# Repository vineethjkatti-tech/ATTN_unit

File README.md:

# ATTN_unit
A smart desk companion that tracks your focus using sound, motion, and time. It gives real-time feedback, builds study streaks, and adapts to your habits to help you stay locked in. Stay focused. It’s watching.
It is a device that helps you focus while studying, working etc. The main purpose of this device is to gameify maintaining focus and helps us achieve concentration.

# Overview
Fitted with the **Esp32 Dev Board**, **ATTN_unit** uses **I2S MEMS Breakout Board** and **HLK-LD2410** sensors to read the noise levels and movment of the user and gives out the **Focus Score** of the user and also displays corresponding emotions the **2.13 Inch E-Ink Display**. It includes a **2 pin tactile switch** to start or stop a study session.

## Zine Page

_Check out my zine_page [here!!](https://github.com/vineethjkatti-tech/ATTN_unit/blob/main/ATTN_unit-zine.pdf)

# How it works
This project has four key elements:

**1. Memory**
>It uses an ESP32 so basically in - built memory that stays even after restart. It uses memory data for long term analysis.

**2. Personality:**
>Yes! it has a personality you can influence its personality. For example, if you are distracted a lot of the times it is more stricter on you and if your more focused on the other hand, it is more kind..

**3. Sensor Reading:**
>It reads data from various sensors on the esp namely - microphone(noise level), motion sensor(for your movment sensation) and also a push button(to start or end session).

**4. Reward Logic**
>This the highlight of my project. There is one core factor - **consistency score** which is affected by many factors such as your **focus**, the **noise level** in your environment, your **movment** - how much you fidget around and its **state **_(which is affected by noise level, focus and motion)._

## Firmware Logic
The code contains a lot of **variables** and custom **functions**. It has a **Scoring System** and also contains **Memory**. The UI is good and it contains a character called **EYES** who always keeps watch on you and craves for your **attention**.

### Structure
When we come to the hardware side, ATTN_unit contains two parts:
1. **Part A:** The Front Panel with the screen bezel and the screen itself.
2. **Part B:** The main container that holds the PCB and to which the Part A is snapped onto

**Connection Methods:**
There are two types of connection methods used in this project
1. **Snap-in Locks-**
  - It is used to fit Part A and B together.
  - It is used to fit the display onto its bezel.

2. **M3 Heat Inserts-**
  - They are used to connect the PCB with Part B.

**Display:**
As the **2.13 Inch 2 color E-Ink display** is native to one of the raspberry pi, I have to keep in mind some things while connecting it to ESP32.
The JST on the display accomodates **8-sockets** as you may know. I have provided an **8-pin header** on my PCB which has the same pin designations as the JST on the the display. The JST can be connected to the header using jumper wires. 

# Steps to Build ATTN_unit
**All the required materials to make the project can be found in the BOM file!!**

1. Start by printing all the requires plastic material. (All CAD files can be found [here](https://github.com/vineethjkatti-tech/ATTN_unit/tree/main/CAD))

2. Next, mount the PCB (it doesnt matter if you solder one, you can find all the schematics [here](https://github.com/vineethjkatti-tech/ATTN_unit/tree/main/KICAD)) to the standoffs in **Part B** using **M3 Inserts and Screws**.

3. After that put the display into Part A by just pressing it in ( the Part has snap-in locks in the bezel space ).

4. Then screw an **8mm momentary switch** through the hole in the **right side** of **Part B**. Solder the two pins to their resepctive pins on ESP32 (One to **GND** and another one to any **GPIO pin**)

5. After this connect the **Front Panel** and **Part B** by pressing them into each other cause they have **snap-in locks**.

6. Last step is to connect the ESP32 to a USB Port for Power Supply and your done!!

**_If you followed all the steps, then congrats!! Your ATTN_unit is ready. Enjoy your fulfilling and focus-filled study sessions!!_**

# Why this Project?
In a world with thousands of distractions around us, it is hard for students to focus and concentrate on studying. These study sessions are often plain and lack something **fun**. This lack of _fun_ is satisfied by our **ATTN_unit**. It makes studying feel like a game by introducing **Focus Score** and others such elements that **encourage** students to study.

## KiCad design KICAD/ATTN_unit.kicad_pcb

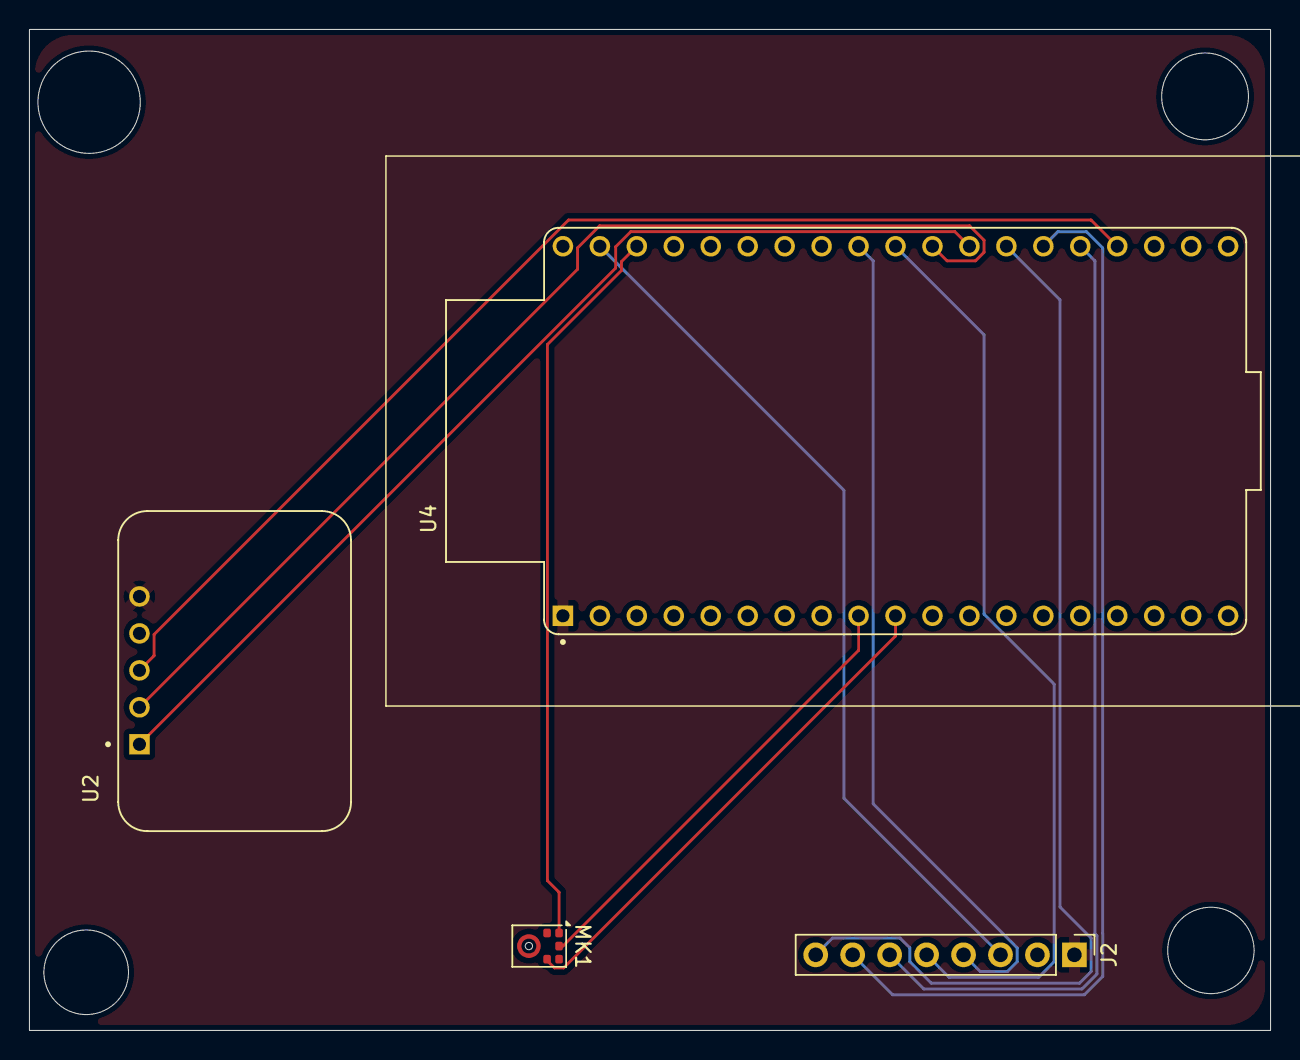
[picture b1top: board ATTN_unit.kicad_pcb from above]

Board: 2 copper layers, 85.3 x 68.8 mm, 4 parts (0 on the bottom side), 14 nets.

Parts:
J2: Screen Connector; PinHeader_1x08_P2.54mm_Vertical
MK1: SPH0645LM4H; Knowles_SPH0645LM4H-6_3.5x2.65mm
U2: HLK-LD2410C; MODULE_HLK-LD2410C
U4: ESP32-DEVKITC-32E; ESP32

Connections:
unnamed: J2.8 (BUSY), U4.J3_13 (IO4)
unnamed: J2.4 (CLK), U4.J3_9 (IO18)
unnamed: J2.5 (CS), U4.J3_10 (IO5)
unnamed: J2.6 (DC), U4.J3_15 (IO2)
unnamed: J2.3 (DIN), U4.J3_2 (IO23)
unnamed: J2.2 (GND), MK1.2 (SEL), MK1.3 (GND), U2.4 (GND), U4.J3_1 (GND_J3_1)
unnamed: J2.7 (RST), U4.J3_14 (IO0)
unnamed: J2.1 (VCC), MK1.5 (VDD), U2.5 (VCC), U4.J2_1 (3V3)
unnamed: MK1.4 (BCLK), U4.J2_10 (IO26)
unnamed: MK1.6 (DATA), U4.J2_9 (IO25)
unnamed: MK1.1 (WS), U4.J3_3 (IO22)
unnamed: U2.3 (OUT), U4.J3_16 (IO15)
unnamed: U2.2 (UART_RX), U4.J3_11 (IO17)
unnamed: U2.1 (UART_TX), U4.J3_12 (IO16)

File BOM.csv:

Name ,Qty,Price ($),Link
KY038 Sensor,1,1.88,https://www.amazon.in/roboCraze-Robocraze-Sound-Sensor-Modul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
Tactile Switch (2 pin),1,0.1,https://www.amazon.in/Push-Button-Tactile-Micro-Switch/dp/B0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
0.96 inch OLED display,1,2.18,https://robu.in/product/0-96-inch-ssd1306-white-oled-display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
HLK-LD2410C Sensor,1,5.26,https://robu.in/product/hi-link-hlk-ld2410c-p-24ghz-human-pr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
ESP32-DEVKITC-32E,1,3.54,https://robu.in/product/esp-wroom-32-esp32-wifi-bt-ble-mcu-module/
M2 Inserts,8,0.4,https://robu.in/product/m2-x-4-mm-brass-insert/
M2 Screws,8,0.7,https://robu.in/product/m2-x-8mm-socket-button-head-cap-alle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
M3 Inserts,4,0.24,https://www.amazon.in/Insert-Threaded-Printing-Woodworking-P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
M3 Screws,4,0.212,https://www.amazon.in/Rpi-shop-tensile-Machine-Quantity/dp/B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
Shipping Costs,-,~10,-
Grand Total ,,24.512,-

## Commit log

2026-05-01 Create hi
2026-05-01 Fix grammar and clarity in README personality section
    Corrected grammatical errors and improved clarity in the personality section.
2026-05-01 Fix typos and enhance formatting in README
    Corrected typos and improved formatting in the README.
2026-05-11 Added Large Files
2026-05-11 Add 'Why this Project?' section to README
    Added a section explaining the purpose of the project.
2026-05-12 Add image to README for device illustration
    Added an image to illustrate the device's features.
2026-05-12 Fix typo in README.md
2026-05-12 Update README with build steps and resources
    Added instructions for building the ATTN_unit and included links to design and CAD files.
2026-05-13 Fix typo in README about character 'EYES'
    Corrected a typo in the README regarding the character 'EYES'.
2026-05-13 Deleted Duplicates and Organized Repository.
2026-05-13 Rename ATTN_unit.csv to BOM.csv
2026-05-17 Add pixel art light bulb simulator
    - Created a new `simulator/` directory.
    - Implemented `index.html`, `style.css`, and `script.js`.
    - Used CSS box-shadow technique for pixel art representation of Standard, Edison, and Globe bulbs.
    - Added power toggle and bulb type selection functionality.
    - Verified with Playwright screenshots and video.
2026-05-26 Correct sensor and display information in README
    Updated sensor details and display type in the README.
2026-05-26 Update README with hardware structure and connections
    Added sections on structure and connection methods for ATTN_unit.
2026-05-27 Changed Files
2026-05-28 Revise README with new images and connection methods
    Updated images and added connection methods and display details.
2026-05-28 Update zine image in README
    Replaced the old zine image with a new one.
2026-05-29 Arranged the Repository
2026-05-29 Fix zine page link in README
    Updated the link to the zine page in the README.
2026-05-29 Update README with display connection instructions
    Added instructions for connecting the display to the PCB.
2026-05-29 Enhance README with gallery and project explanation
    Added a gallery section with images for pinout schematic and display connection.
2026-05-29 Fix typo in README.md regarding plastic material
2026-05-29 Clarify firmware logic description in README
    Updated the description of firmware logic for clarity.
2026-05-30 Revise firmware logic and UI description
    Updated description of firmware logic and UI elements.
2026-05-30 Revise README for ATTN_unit specifications
    Updated device description and switch type in README.
2026-05-30 Fix formatting of zine page link in README
2026-05-30 Update README to improve firmware logic description
    Clarified the description of the UI display and its functionality.
2026-05-30 Update README with E-Ink display connection details
    Clarified the compatibility of the E-Ink display with Raspberry Pi and ESP32.
2026-05-30 Clarify 3D model used in CAD for display
    Added a note regarding the 3D model used in the CAD.
2026-05-30 Improve clarity and details in README.md
    Updated the README to clarify personality influence, sensor descriptions, and reward logic details.
2026-05-30 Edit README for clarity and grammar fixes
    Corrected minor grammatical errors and improved clarity in the README.
2026-05-30 Fix grammatical errors in README.md
2026-06-13 Change Files
2026-06-27 Document PCB design process and encountered issues
    Added details about PCB design process and challenges faced, including missing footprints and pin assignments.
2026-06-27 Update README with manual review note and link
    Added a note about manual review and linked journal.md.
2026-06-27 Mention AI usage in project
    Added a note about AI usage in the project.
